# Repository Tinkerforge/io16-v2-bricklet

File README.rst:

IO-16 Bricklet 2.0
==================

This repository contains the firmware source code and the hardware design
files. The documentation generator configs can be found at
https://github.com/Tinkerforge/generators

Repository Content
------------------

software/:
 * examples/: Examples for all supported languages
 * build/: Compiled files
 * src/: Source code of firmware
 * Makefile: Makefile to build project

hardware/:
 * Contains KiCad project files and additionally schematics as PDF

datasheets/:
 * Contains datasheets for sensors and complex ICs that are used

Hardware
--------

The hardware is designed with the open source EDA Suite KiCad
(http://www.kicad.org). Before you are able to open the files,
you have to install the Tinkerforge kicad-libraries
(https://github.com/Tinkerforge/kicad-libraries). You can either clone
them directly in hardware/ or clone them in a separate folder and
symlink them into hardware/
(ln -s kicad_path/kicad-libraries project_path/hardware). After that you
can open the .pro file in hardware/ with KiCad and from there view and
modify the schematics and the PCB layout.

Software
--------

If you want to do your own Brick/Bricklet firmware development we highly
recommend that you use our build environment setup script and read the
tutorial (https://www.tinkerforge.com/en/doc/Tutorials/Tutorial_Build_Environment/Tutorial.html).

To compile the C code we recommend you to install the newest GNU Arm Embedded
Toolchain (https://launchpad.net/gcc-arm-embedded/+download).
You also need to install bricklib2 (https://github.com/Tinkerforge/bricklib2).

You can either clone it directly in software/src/ or clone it in a
separate folder and symlink it into software/src/
(ln -s bricklib_path/bricklib2 project_path/software/src/). Finally make sure to
have CMake installed (http://www.cmake.org/cmake/resources/software.html).

After that you can build the firmware by invoking make in software/.
The firmware (.zbin) can then be found in software/build/ and uploaded
with brickv (click button "Flashing" on start screen).

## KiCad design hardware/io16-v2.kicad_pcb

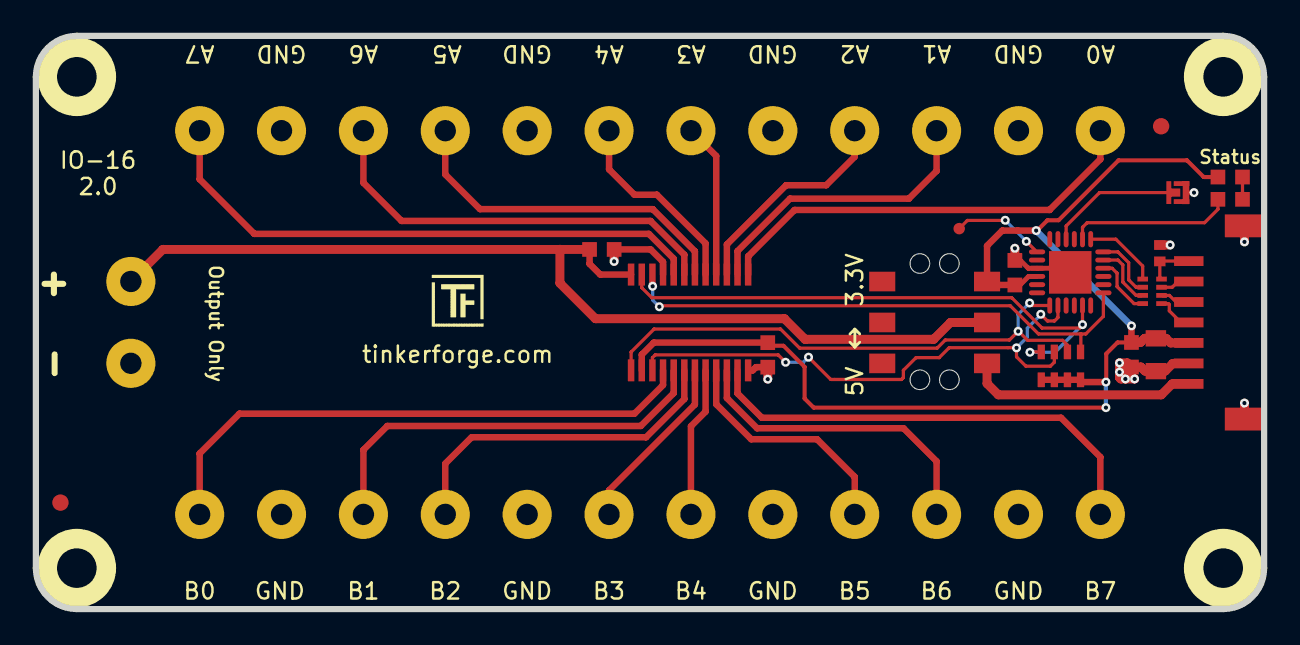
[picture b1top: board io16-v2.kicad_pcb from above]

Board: 2 copper layers, 75.0 x 35.0 mm, 38 parts (0 on the bottom side), 36 nets.

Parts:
C1: 10uF; C0805
C2, C3, C6: 100nF; C0603F
C4: 220pF; C0402F
C5: 1uF; C0603F
D1: blue; D0603F
Fiducial_Mark: VAL**; Fiducial_Mark
Fiducial_Mark#2: VAL**; Fiducial_Mark
J1, J2, J3, J4, J5, J6, J7, J8, J9, J10, J11, J12, J13: AKL_5_2
P1: CON-SENSOR2
P2: DEBUG; DEBUG_PAD
P3: BOOT; SolderJumper
R1: 1k; R0603F
RP1: 2k2; 4X0603
RP2: 82; 4X0402
Ref**: Val**; Logo_31x31
SW1: Power_Select; SLIDE_SWITCH
U1: XMC1100; QFN24-4x4mm-0.5mm
U4, U5, U6, U7: DRILL; DRILL_NP
U8: PCAL6416APW; TSSOP24-44
VAL: CE_5mm
VAL#2: WEEE_7mm

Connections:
+5V: P1.1, SW1.1
GND: C1.2, C2.2, C3.1, C4.2, C5.2, C6.2, J1.1, J2.1, J4.2, J5.1, J7.2, J8.2, J10.1, J11.2, J13.1, P1.2, P1.EP, P3.1, U1.9, U1.EXP, U8.12, U8.21
INT: RP1.7, U1.13, U8.1
unnamed: C4.1, P1.7, RP2.4
unnamed: D1.2, R1.2
unnamed: J2.2, U8.4
unnamed: J3.1, U8.6
unnamed: J3.2, U8.5
unnamed: J4.1, U8.7
unnamed: J5.2, U8.8
unnamed: J6.1, U8.10
unnamed: J6.2, U8.9
unnamed: J7.1, U8.11
unnamed: J8.1, U8.20
unnamed: J9.1, U8.19
unnamed: J9.2, U8.18
unnamed: J10.2, U8.17
unnamed: J11.1, U8.16
unnamed: J12.1, U8.15
unnamed: J12.2, U8.14
unnamed: J13.2, U8.13
unnamed: P1.4, RP2.1
unnamed: P1.5, RP2.2
unnamed: P1.6, RP2.3
unnamed: P2.1, U1.7
unnamed: P3.2, U1.4
unnamed: R1.1, U1.2
RESET: RP1.6, U1.14, U8.3
S-CLK: RP2.7, U1.23
S-CS: RP2.8, U1.22
S-MISO: RP2.5, U1.1
S-MOSI: RP2.6, U1.24
SCL: RP1.8, U1.19, U8.22
SDA: RP1.5, U1.17, U8.23
VAA: C3.2, J1.2, SW1.2, U8.24
VCC: C1.1, C2.1, C5.1, C6.1, D1.1, P1.3, RP1.1, RP1.2, RP1.3, RP1.4, SW1.3, U1.10, U8.2

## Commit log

2018-03-05 Add datasheet
2018-03-06 Add initial schematic
2018-03-06 Assign all footprints
2018-03-06 Add layout
2018-03-06 Add Tinkerforge-CoMCU logo
2018-03-13 Fix silkscreen text
2018-04-05 Add initial auto-generated stub firmware
2018-04-05 Add .gitignore
2018-04-05 Set correct led, boot, debug pins
2018-04-10 Add driver for PCAL6416A
2018-04-11 specify I2C pullup value
2018-04-12 Remove debug
2018-04-12 Make sure that an I2C error resets I2C, but does not change the PCAL6416A configuration
2018-04-12 Use 400kHz baudrate
2018-04-13 Firmware implementation
2018-04-13 Fix pcal6416a driver
2018-04-13 Fix all input value CB logic
2018-04-13 Add tests
2018-04-17 Implement some space saving measures.
    The firmware became too big after we added timeout/i2c clear support
    to the bricklib2 i2c fifo
2018-05-11 Rename files
2018-05-29 Remove unnecessary get-selected-value function
2018-06-06 set origin
2018-06-18 Change capacitor footprint(s) to C0402F
2018-06-26 fix text
2018-06-28 Fix readme
2018-07-11 Add Makefile with docker support
2018-07-11 Update directory structure and build instructions
2018-07-11 Remove obsolete generate_makefile scripts
2018-07-16 Decrease EEPROM emulation size to 256
    This saves some bytes in the firmware, so it builds with older gcc versions
2018-07-17 specify processor
2018-07-31 Add 3d models (*.FCStd & *.step)
2018-07-31 Add PDF schematic
2018-09-11 Add auto-generated examples
2018-09-14 examples: Adapt callback config to common style
2018-09-14 examples: Fix typo in comment
2018-09-20 specify multiplexer ic
2018-10-05 Add rev to changelog
2018-10-16 Remove in-development marker
2018-11-06 Add rust examples
2018-11-07 rust: Accept host names for ip connection, fix naming inconsistencies
2018-11-07 rust: Rename callback receivers.
2018-12-14 Add go examples.
2018-12-18 go: Change import path.
2018-12-18 go: Change import path again.
2018-12-20 rust: Reformat examples.
2019-01-24 mqtt: Add examples.
2019-01-24 mqtt: Fix example header.
2019-01-24 mqtt: Remove executable bit in example permissions.
2019-01-24 go: Minor example fixes.
2019-01-24 mqtt: Minor example fixes.
2019-01-29 rust: Fix unused loop index.
2019-03-28 mqtt: Fix whitespace.
2019-05-07 Abort active monoflop on set-(selected-)value call
    Don't clear monoflop time on monoflop done/abort to match documentation.
2019-05-29 Increase version for new release (changes in bricklib2)
2019-06-13 specify processor, fix references
2019-08-22 c: Adapt to bindings changes
2020-01-13 examples: Use python3 input instead of python2 raw_input.
2020-01-13 examples: mqtt: Remove trailing whitespace.
2020-03-16 Whitespace
2020-03-23 mqtt: Update for loop style
2020-04-07 examples: rust: Always block when calling bindings functions.
2020-08-19 Add uc examples.
2020-08-25 uc: Fix whitespace
2020-08-27 uc: Fix warnings.
2020-08-31 uc: Use fixed-with placeholders in format strings.
2020-09-02 uc: Add example driver note.
2021-05-06 Add input example
2021-10-25 Update KiCad link
    https://www.kicad.org/blog/2021/10/Avoid-links-to-former-kicad-domain/
2022-04-19 examples: uc: Rename TF_HalContext to TF_HAL.
2022-04-27 uc: Adapt to bindings changes
2022-05-10 go: Fix format string
2022-07-06 Add license files.
2025-10-04 Fix compatibility with new Docker build image (GCC 14.2.1)

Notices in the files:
hardware/io16-v2.kicad_pcb:
Licensed under CERN OHL v.1.1
Copyright (©) 2018, L.Lauer
Copyright Tinkerforge GmbH 2018.
This documentation describes Open Hardware and is licensed under the
CERN OHL v. 1.1.
